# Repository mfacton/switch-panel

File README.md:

# External USB Switches and OLED

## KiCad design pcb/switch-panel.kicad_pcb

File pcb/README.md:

## BOM
[0805 LED pack](https://www.amazon.com/AEDIKO-Lighting-Electronics-Components-Emitting/dp/B09XB62ST5/ref=sr_1_3?crid=199NJCK6SFZ6L&dib=eyJ2IjoiMSJ9.DeAxoe01pJBBlihK29cn42YpX7peseVYEhGwAf6ccEPyct4X4PbH5IbdXQiKTQA0LWOeMrwrHhpW2EvpB2AtVONWaWH3MDPvv71KHXA9JyfJrWusn1znHVTfl4g_-NYjQChLNOlRj0tysgzI-TyEemvupWWNMid4XB7WfoHm2oo5oW9p9P8tgbA6DG-g-5MdyDMecx6z0xvQRTZBTQmGDIYLU98AAbTIcijbL8EPMhQ.rQZe9JyVD1LPC98fB-9kU1f3Qj-90xt3Ci5htq9ja1U&dib_tag=se&keywords=smd%2Bled%2B0805&qid=1716414656&sprefix=smd%2Bled%2Caps%2C81&sr=8-3&th=1)

[MX Mechanical Switches](https://www.amazon.com/Switches-Underglow-Compatible-Mechanical-Transparent/dp/B07K82PKJK/ref=sr_1_4?crid=3H8B7LF7PSAYN&dib=eyJ2IjoiMSJ9.hj6_K2hiGFvL7RZv6BjQvE_8Tkyj3AgwYeoPc3CJGCKzz0qMmNYSFBjPL2O9GOt7N3JpybKFIjDQv1pKPM2mjX431uuvvkPLLKAOLOdDwXrVIsHMTV4Ba1Gbvb5xP26fazgtT4Y9BMmsfDzz9XSpFvngvS68hAWX7OJesAa1HNGLu3syzBRnPdVPFXXiV1uQ-wEbLpsFg2-yyOM7M925uE2NngphyuZ8kbCJ3o5rbh0.7TRLV2TTzbj2r7PpN1yHdIpEJ0eGGW8-26CgTdLXAjY&dib_tag=se&keywords=mx%2Bswitch%2Bwith%2Bled&qid=1716405545&sprefix=mx%2Bswitch%2Bwith%2Ble%2Caps%2C112&sr=8-4&th=1)

[MX Keycaps](https://www.amazon.com/Elacgap-Profile-switches-Mechanical-Keyboard/dp/B0CQ2XG16M/ref=sr_1_8?crid=2RP28D32T4YI7&dib=eyJ2IjoiMSJ9.g8jvMC9cZL7gfZqPBhRIdKUHe3eb-S7Zu2OdtOTq91nK9_iQPxGGtbLLTdQugAKkmpOXe0Nkh1FkK8IwPvcGJ-i8uOnRT9VaAqVbNe_BFLvqwJAmYfmkC9kHMe8K5EaZz4EmGNwPsFaDcOky1aXE_my7FMzT-e8g7TYaOcDuEcDPOiLBS-DBO3_SYU8wgrV-pp_YsZqSFAQfqK2uji-1JYOTLx0_0cVCY5VA_-yKcgI.tAzjtVK2Q3oeRow_702AohuqjuLbzh1HKoen5f76T84&dib_tag=se&keywords=cherry%2Bmx%2Bkeycaps&qid=1716414879&sprefix=cherry%2Bmx%2Bkeycaps%2Caps%2C64&sr=8-8&th=1)

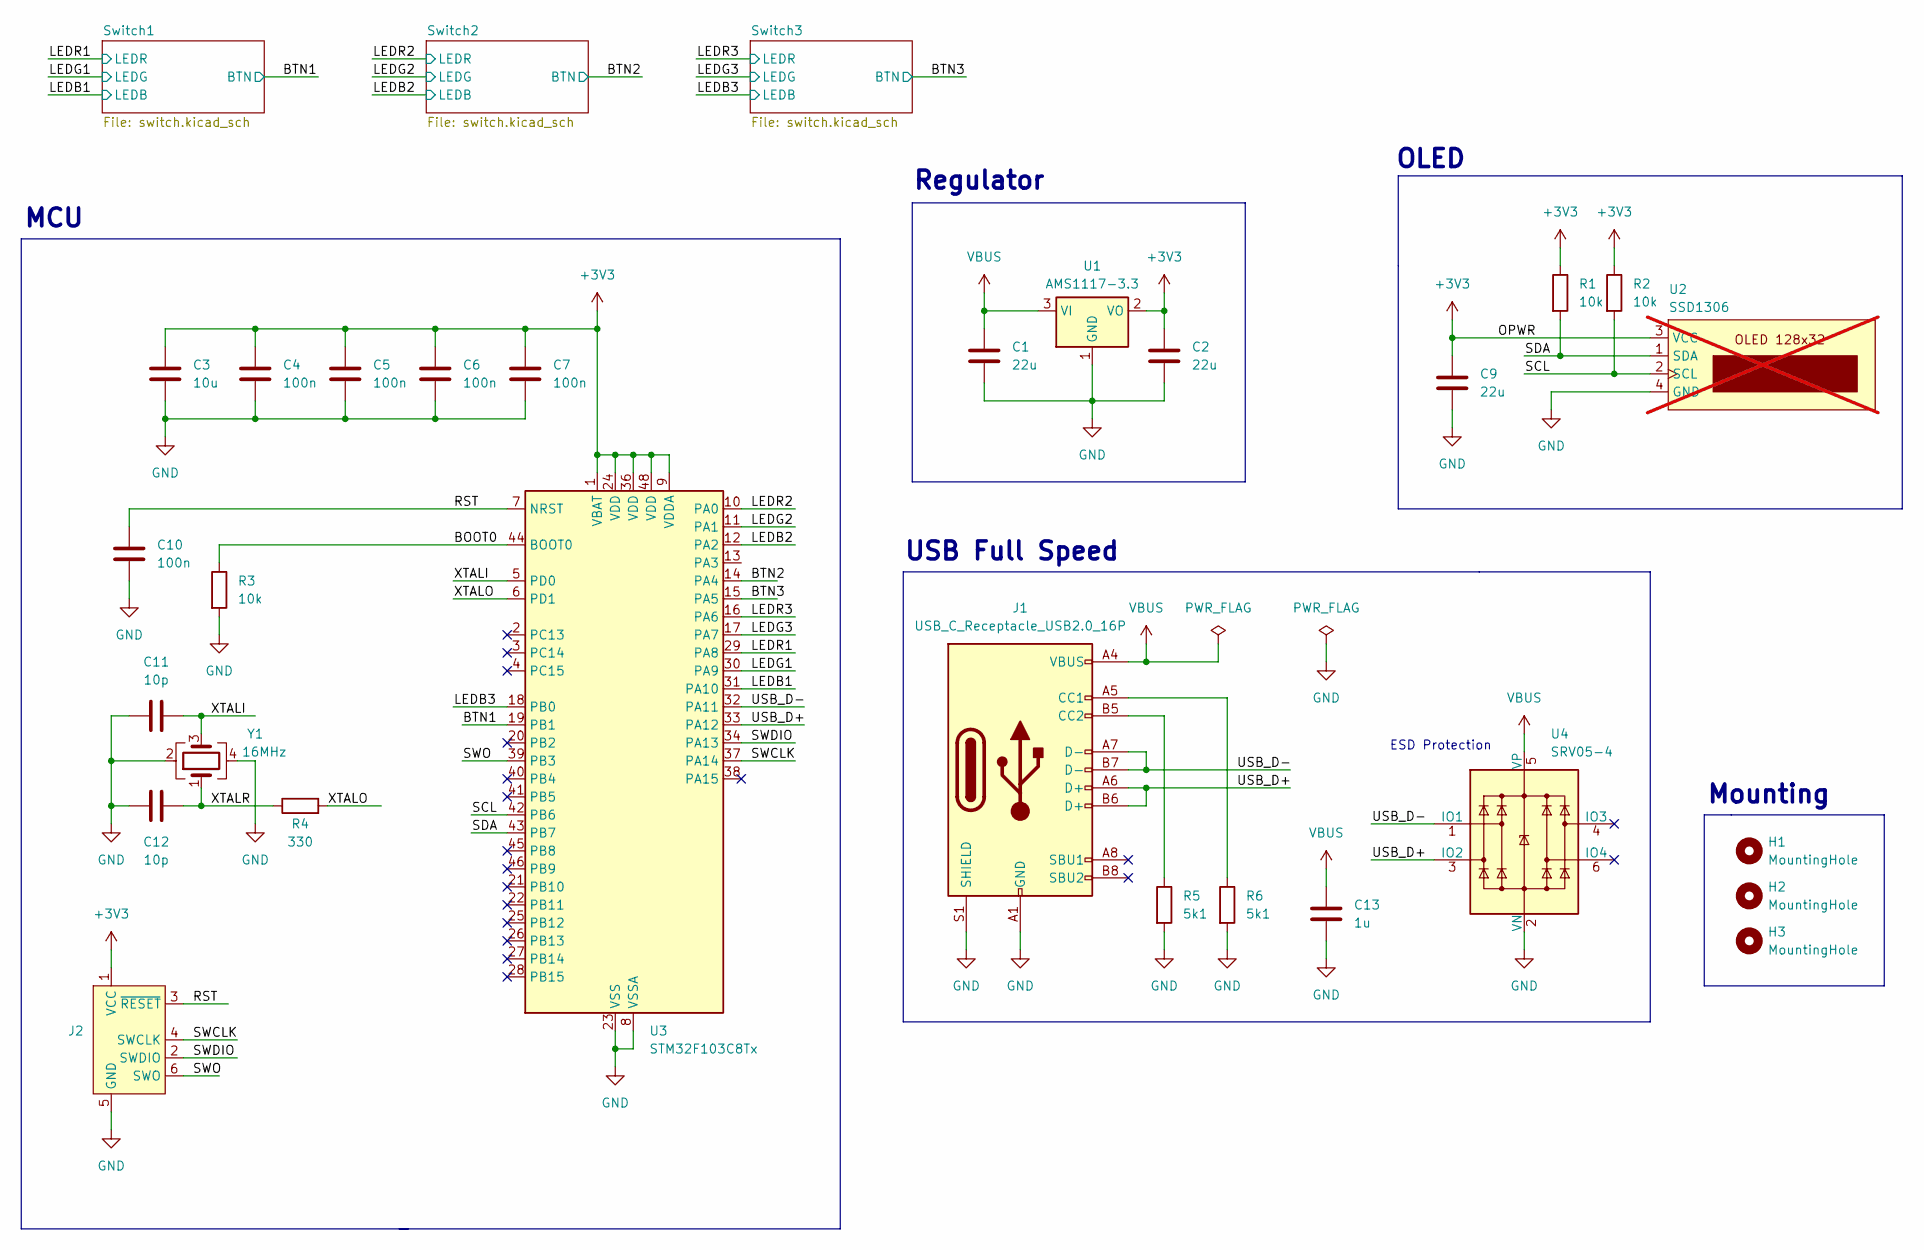
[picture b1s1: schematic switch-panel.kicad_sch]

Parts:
C1: 22u; C_0805_2012Metric
C2, C9: 22u; C_0603_1608Metric
C3: 10u; C_0603_1608Metric
C4, C5, C6, C7, C10: 100n; C_0402_1005Metric
C11, C12: 10p; C_0402_1005Metric
C13: 1u; C_0402_1005Metric
H1, H2, H3: MountingHole; MountingHole_3.2mm_M3
J1: USB_C_Receptacle_USB2.0_16P; USB_C_Receptacle_GCT_USB4105-xx-A_16P_TopMnt_Horizontal; LCSC C165948
J2: Conn_ARM_SWD_TagConnect_TC2030-NL; Tag-Connect_TC2030-IDC-NL_2x03_P1.27mm_Vertical
R1, R2, R3: 10k; R_0402_1005Metric
R4: 330; R_0402_1005Metric
R5, R6: 5k1; R_0402_1005Metric
U1: AMS1117-3.3; SOT-223-3_TabPin2
U2: SSD1306; PinHeader_1x04_P2.54mm_Vertical; not fitted
U3: STM32F103C8Tx; LQFP-48_7x7mm_P0.5mm
U4: SRV05-4; SOT-23-6; LCSC C7420376
Y1: 16MHz; Crystal_SMD_3225-4Pin_3.2x2.5mm

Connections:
+3V3: C2.1, C3.1, C4.1, C5.1, C6.1, C7.1, C9.1, J2.1 (VCC), R1.1, R2.1, U1.2 (VO), U2.3 (VCC), U3.1 (VBAT), U3.9 (VDDA), U3.24 (VDD), U3.36 (VDD), U3.48 (VDD)
/BOOT0: R3.1, U3.44 (BOOT0)
/BTN1: U3.19 (PB1); also elsewhere on the board
/BTN2: U3.14 (PA4); also elsewhere on the board
/BTN3: U3.15 (PA5); also elsewhere on the board
/LEDB1: U3.31 (PA10); also elsewhere on the board
/LEDB2: U3.12 (PA2); also elsewhere on the board
/LEDB3: U3.18 (PB0); also elsewhere on the board
/LEDG1: U3.30 (PA9); also elsewhere on the board
/LEDG2: U3.11 (PA1); also elsewhere on the board
/LEDG3: U3.17 (PA7); also elsewhere on the board
/LEDR1: U3.29 (PA8); also elsewhere on the board
/LEDR2: U3.10 (PA0); also elsewhere on the board
/LEDR3: U3.16 (PA6); also elsewhere on the board
/RST: C10.1, J2.3 (~RESET), U3.7 (NRST)
/SCL: R2.2, U2.2 (SCL), U3.42 (PB6)
/SDA: R1.2, U2.1 (SDA), U3.43 (PB7)
/SWCLK: J2.4 (SWCLK), U3.37 (PA14)
/SWDIO: J2.2 (SWDIO), U3.34 (PA13)
/SWO: J2.6 (SWO), U3.39 (PB3)
/USB_D+: J1.A6 (D+), J1.B6 (D+), U3.33 (PA12), U4.3 (IO2)
/USB_D-: J1.A7 (D-), J1.B7 (D-), U3.32 (PA11), U4.1 (IO1)
/XTALI: C11.2, U3.5 (PD0), Y1.3
/XTALO: R4.2, U3.6 (PD1)
/XTALR: C12.2, R4.1, Y1.1
GND: C1.2, C2.2, C3.2, C4.2, C5.2, C6.2, C7.2, C9.2, C10.2, C11.1, C12.1, C13.2, J1.A1 (GND), J1.A12 (GND), J1.B1 (GND), J1.B12 (GND), J1.S1 (SHIELD), J2.5 (GND), R3.2, R5.2, R6.2, U1.1 (GND), U2.4 (GND), U3.8 (VSSA), U3.23 (VSS), U3.35 (VSS), U3.47 (VSS), U4.2 (VN), Y1.2, Y1.4; also elsewhere on the board
unnamed: J1.A5 (CC1), R6.1
unnamed: J1.B5 (CC2), R5.1
VBUS: C1.1, C13.1, J1.A4 (VBUS), J1.A9 (VBUS), J1.B4 (VBUS), J1.B9 (VBUS), U1.3 (VI), U4.5 (VP); also elsewhere on the board

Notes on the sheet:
Regulator
OLED
MCU
Mounting
USB Full Speed
ESD Protection

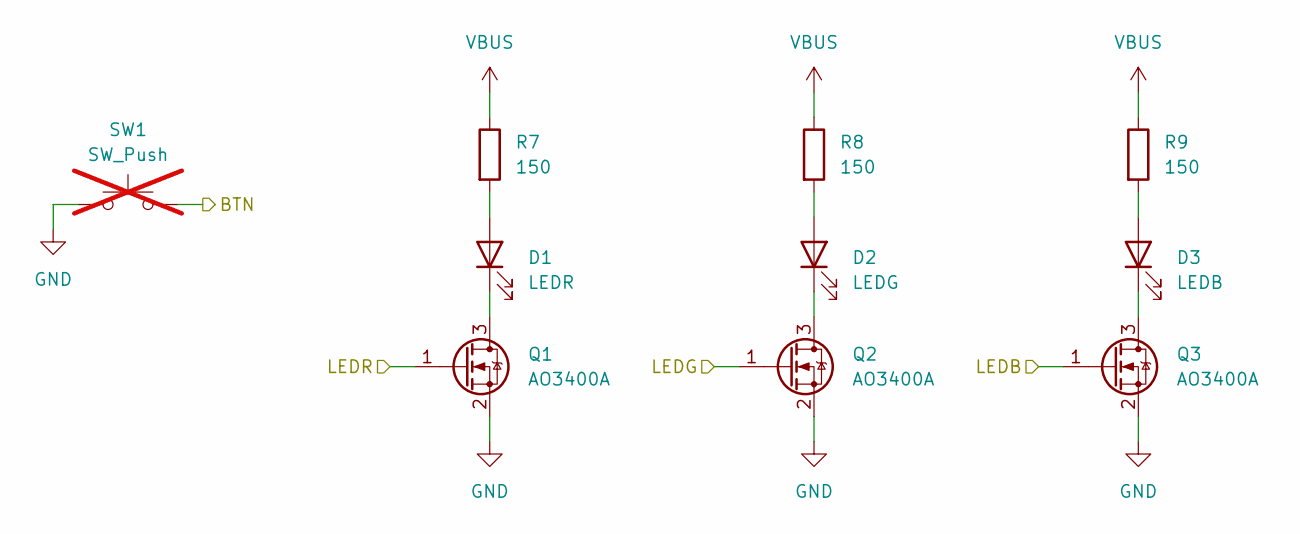
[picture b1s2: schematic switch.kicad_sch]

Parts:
D1: LEDR; LED_0805_2012Metric; LCSC C84256
D2: LEDG; LED_0805_2012Metric; LCSC C2297
D3: LEDB; LED_0805_2012Metric; LCSC C2985984
Q1, Q2, Q3: AO3400A; SOT-23; LCSC C20917
R7, R8, R9: 150; R_0603_1608Metric; LCSC C22808
SW1: SW_Push; SW_Cherry_MX_1.00u_PCB; not fitted

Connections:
/BTN1: SW1.2; also elsewhere on the board
/LEDB1: Q3.1 (G); also elsewhere on the board
/LEDG1: Q2.1 (G); also elsewhere on the board
/LEDR1: Q1.1 (G); also elsewhere on the board
GND: Q1.2 (S), Q2.2 (S), Q3.2 (S), SW1.1; also elsewhere on the board
unnamed: D1.2 (A), R7.2
unnamed: D1.1 (K), Q1.3 (D)
unnamed: D2.2 (A), R8.2
unnamed: D2.1 (K), Q2.3 (D)
unnamed: D3.2 (A), R9.2
unnamed: D3.1 (K), Q3.3 (D)
VBUS: R7.1, R8.1, R9.1; also elsewhere on the board

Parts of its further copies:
D4, D7: LEDR; LED_0805_2012Metric; LCSC C84256
D5, D8: LEDG; LED_0805_2012Metric; LCSC C2297
D6, D9: LEDB; LED_0805_2012Metric; LCSC C2985984
Q4, Q5, Q6, Q7, Q8, Q9: AO3400A; SOT-23; LCSC C20917
R10, R11, R12, R13, R14, R15: 150; R_0603_1608Metric; LCSC C22808
SW2, SW3: SW_Push; SW_Cherry_MX_1.00u_PCB; not fitted

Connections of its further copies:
/BTN2: SW2.2; also elsewhere on the board
/BTN3: SW3.2; also elsewhere on the board
/LEDB2: Q6.1 (G); also elsewhere on the board
/LEDB3: Q9.1 (G); also elsewhere on the board
/LEDG2: Q5.1 (G); also elsewhere on the board
/LEDG3: Q8.1 (G); also elsewhere on the board
/LEDR2: Q4.1 (G); also elsewhere on the board
/LEDR3: Q7.1 (G); also elsewhere on the board
GND: Q4.2 (S), Q5.2 (S), Q6.2 (S), Q7.2 (S), Q8.2 (S), Q9.2 (S), SW2.1, SW3.1; also elsewhere on the board
unnamed: D4.2 (A), R10.2
unnamed: D4.1 (K), Q4.3 (D)
unnamed: D5.2 (A), R11.2
unnamed: D5.1 (K), Q5.3 (D)
unnamed: D6.2 (A), R12.2
unnamed: D6.1 (K), Q6.3 (D)
unnamed: D7.2 (A), R13.2
unnamed: D7.1 (K), Q7.3 (D)
unnamed: D8.2 (A), R14.2
unnamed: D8.1 (K), Q8.3 (D)
unnamed: D9.2 (A), R15.2
unnamed: D9.1 (K), Q9.3 (D)
VBUS: R10.1, R11.1, R12.1, R13.1, R14.1, R15.1; also elsewhere on the board

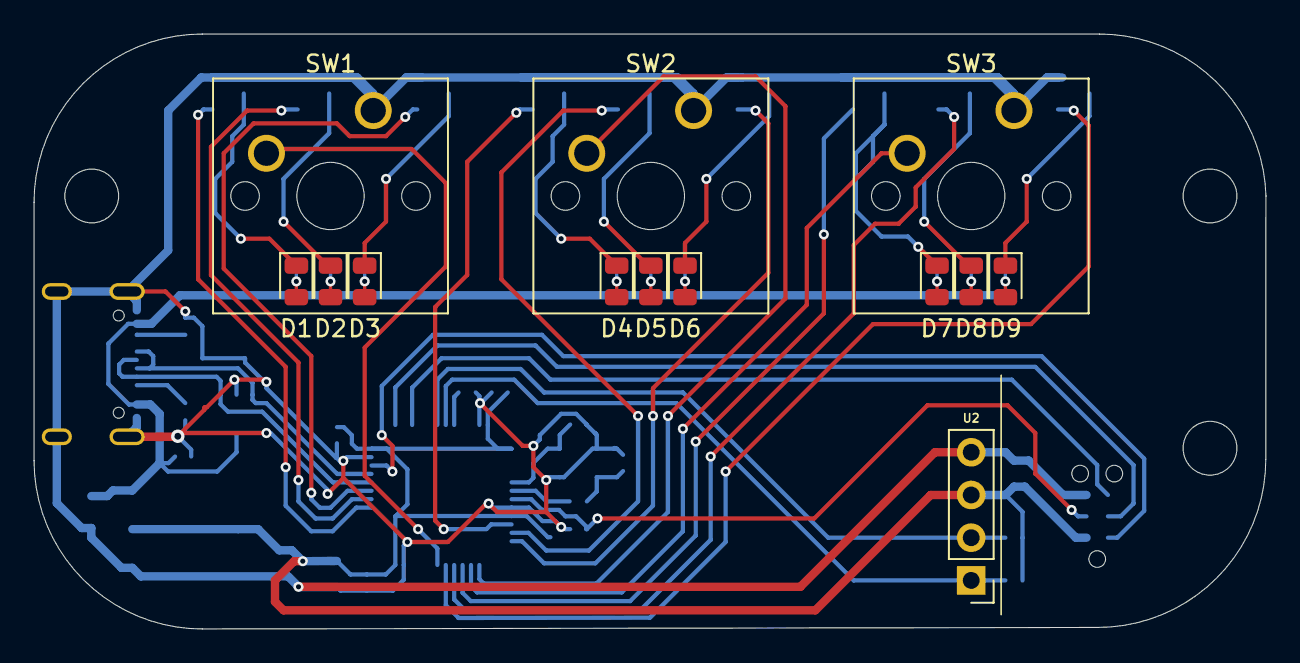
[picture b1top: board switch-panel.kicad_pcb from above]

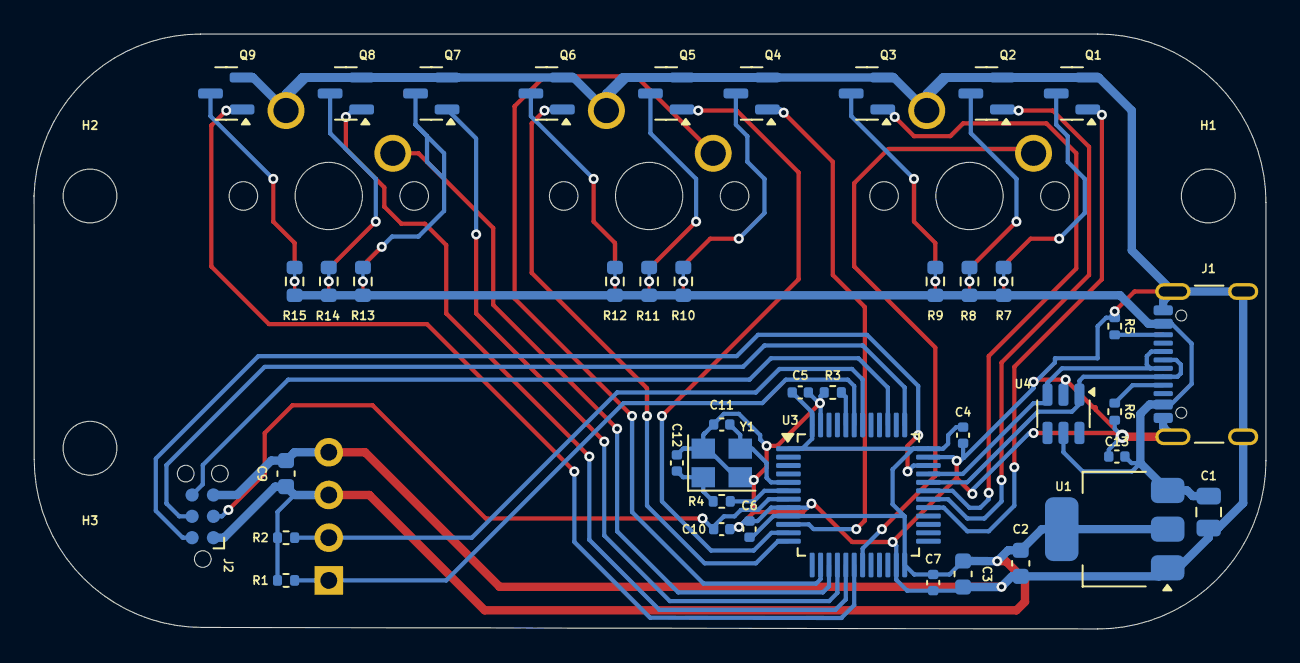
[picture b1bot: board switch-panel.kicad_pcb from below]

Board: 2 copper layers, 73.3 x 35.4 mm, 58 parts (45 on the bottom side), 47 nets.

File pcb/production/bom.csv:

Designator,Footprint,Quantity,Value,LCSC Part #
C1,0805,1,22u,
"C10, C4, C5, C6, C7",0402,5,100n,
"C11, C12",0402,2,10p,
C13,0402,1,1u,
"C2, C9",0603,2,22u,
C3,0603,1,10u,
"D1, D4, D7",0805,3,LEDR,C84256
"D2, D5, D8",0805,3,LEDG,C2297
"D3, D6, D9",0805,3,LEDB,C2985984
J1,USB_C_Receptacle_GCT_USB4105-xx-A_16P_TopMnt_Horizontal,1,USB_C_Receptacle_USB2.0_16P,C165948
"Q1, Q2, Q3, Q4, Q5, Q6, Q7, Q8, Q9",SOT-23,9,AO3400A,C20917
"R1, R2, R3",0402,3,10k,
"R10, R11, R12, R13, R14, R15, R7, R8, R9",0603,9,150,C22808
R4,0402,1,330,
"R5, R6",0402,2,5k1,
U1,SOT-223-3_TabPin2,1,AMS1117-3.3,
U3,LQFP-48_7x7mm_P0.5mm,1,STM32F103C8Tx,
U4,SOT-23-6,1,SRV05-4,C7420376
Y1,Crystal_SMD_3225-4Pin_3.2x2.5mm,1,16MHz,

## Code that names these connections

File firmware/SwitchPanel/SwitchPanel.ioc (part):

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Mcu.Name=STM32F103C(8-B)Tx
Mcu.Package=LQFP48
Mcu.UserName=STM32F103C8Tx
PA0-WKUP.Signal=S_TIM2_CH1_ETR
PA1.Signal=S_TIM2_CH2
PA10.Signal=S_TIM1_CH3
PA11.Mode=Device
PA11.Signal=USB_DM
PA12.Mode=Device
PA12.Signal=USB_DP
PA13.Mode=Trace_Asynchronous_SW
PA13.Signal=SYS_JTMS-SWDIO
PA14.Mode=Trace_Asynchronous_SW
PA14.Signal=SYS_JTCK-SWCLK
PA2.Signal=S_TIM2_CH3
PA4.GPIOParameters=GPIO_PuPd,GPIO_Label
PA4.GPIO_Label=BTN2
PA4.GPIO_PuPd=GPIO_PULLUP
PA4.Signal=GPIO_Input
PA5.GPIOParameters=GPIO_PuPd,GPIO_Label
PA5.GPIO_Label=BTN3
PA5.GPIO_PuPd=GPIO_PULLUP
PA5.Signal=GPIO_Input
PA6.Signal=S_TIM3_CH1
PA7.Signal=S_TIM3_CH2
PA8.Signal=S_TIM1_CH1
PA9.Signal=S_TIM1_CH2
PB0.Signal=S_TIM3_CH3
PB1.GPIOParameters=GPIO_Label
PB1.GPIO_Label=BTN1
PB1.Signal=GPIO_Input
PB3.Mode=Trace_Asynchronous_SW
PB3.Signal=SYS_JTDO-TRACESWO
PB6.Mode=I2C
PB6.Signal=I2C1_SCL
PB7.Mode=I2C
PB7.Signal=I2C1_SDA
PD0-OSC_IN.Mode=HSE-External-Oscillator
PD0-OSC_IN.Signal=RCC_OSC_IN
PD1-OSC_OUT.Mode=HSE-External-Oscillator
PD1-OSC_OUT.Signal=RCC_OSC_OUT
RCC.HSEDivPLL=RCC_HSE_PREDIV_DIV2
RCC.HSE_VALUE=16000000
RCC.SYSCLKFreq_VALUE=72000000
RCC.SYSCLKSource=RCC_SYSCLKSOURCE_PLLCLK
board=custom

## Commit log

2024-05-22 Add gitignore
2024-05-22 Make schematic components
2024-05-22 Finish schematics
2024-05-22 Setup stm32 cube
2024-05-22 Layout except stm32
2024-05-22 Add BOM
2024-05-22 Add test production files
2024-05-23 Final routing and production
2024-05-23 Add user library
2024-05-23 Finish pinout config
2024-06-06 Remove OS garbage
